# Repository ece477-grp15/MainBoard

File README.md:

# SeniorDesignMainBoard
The main PCB board to run our project

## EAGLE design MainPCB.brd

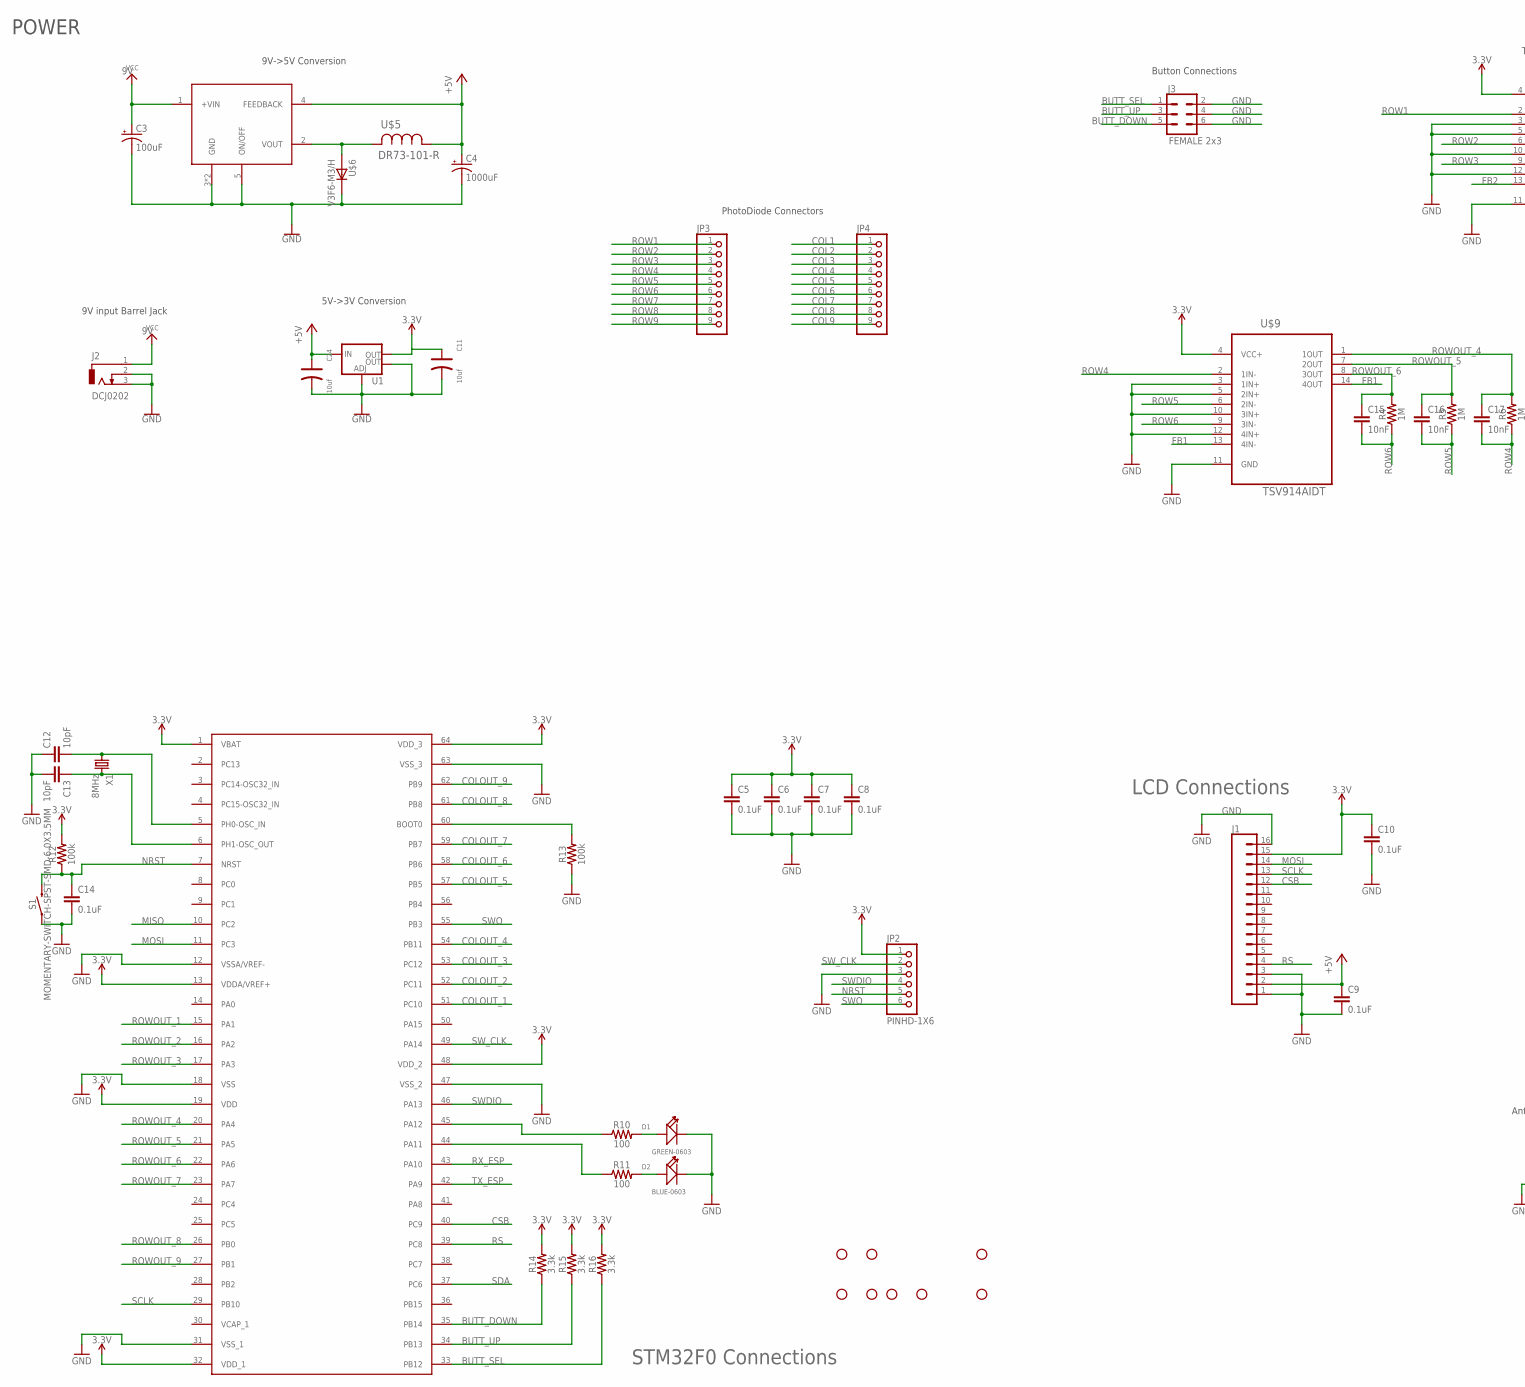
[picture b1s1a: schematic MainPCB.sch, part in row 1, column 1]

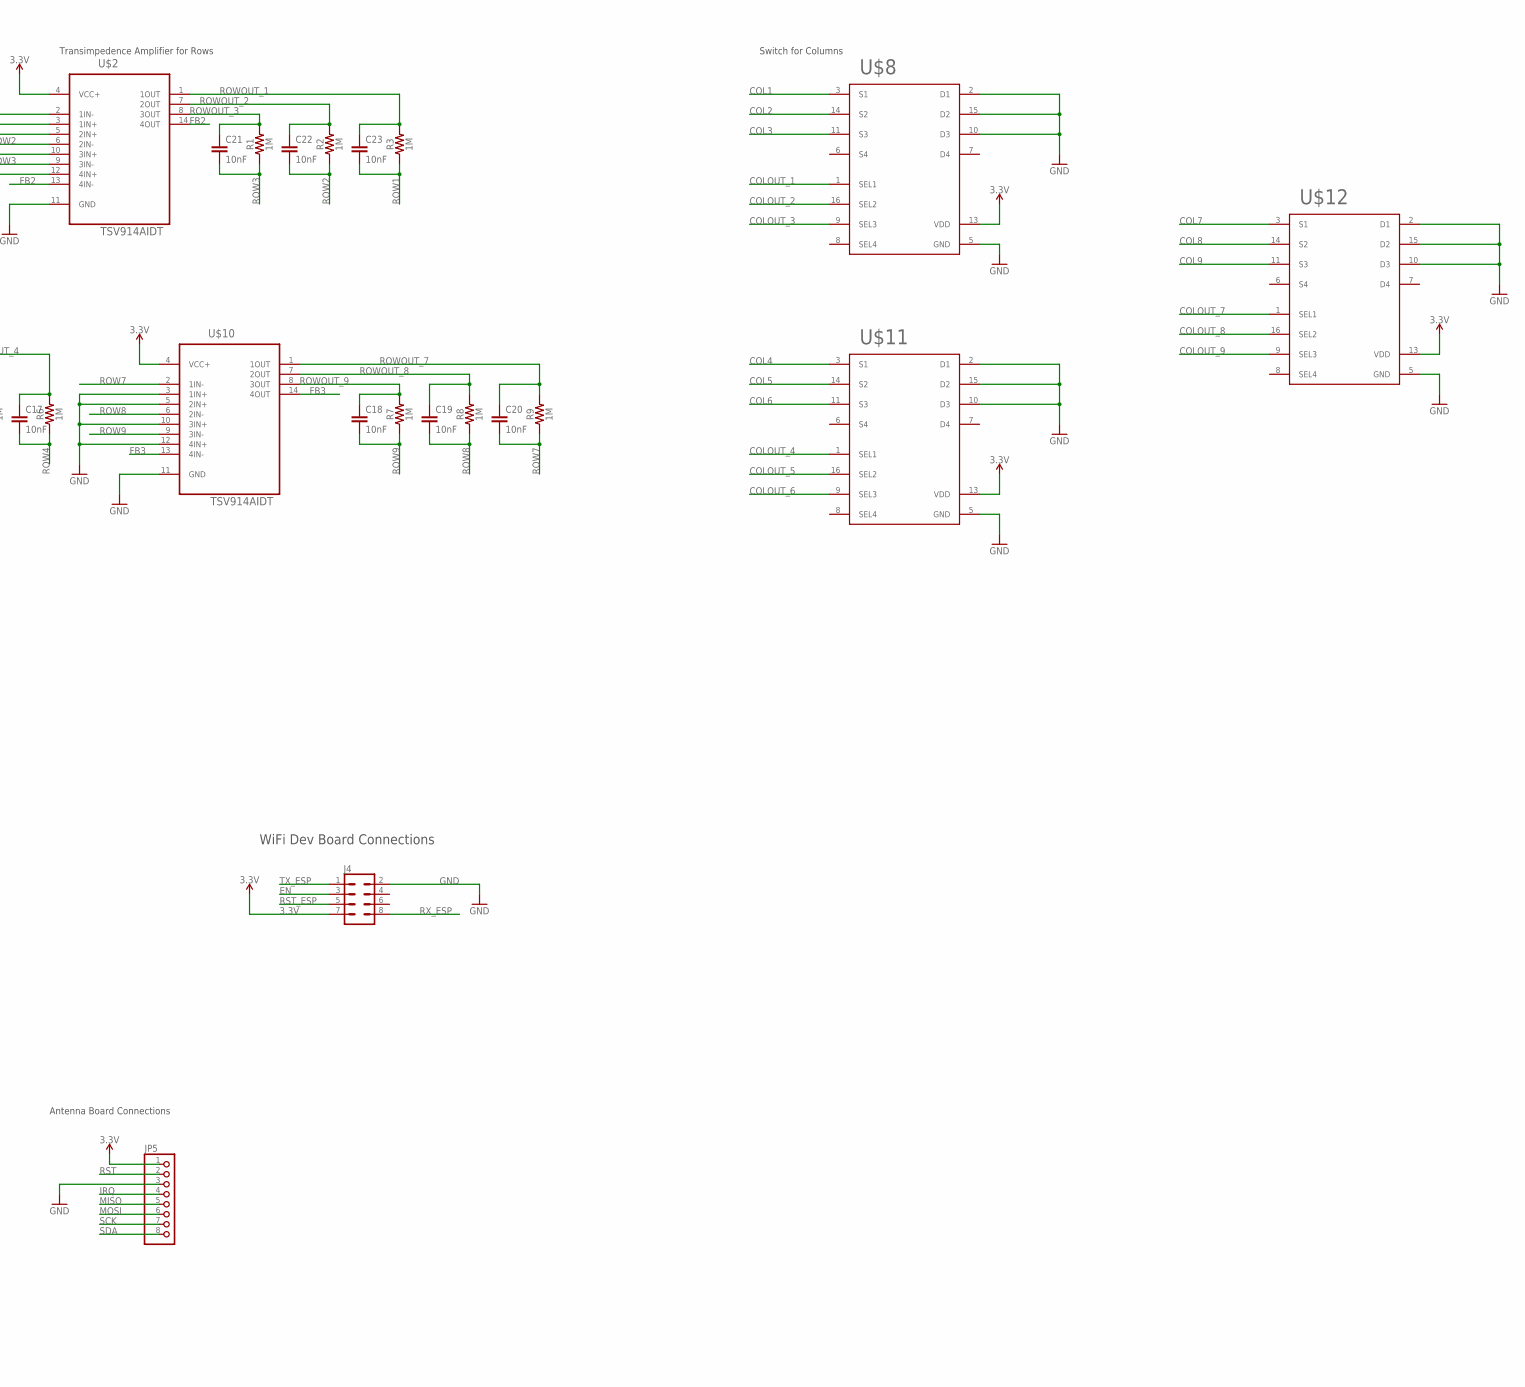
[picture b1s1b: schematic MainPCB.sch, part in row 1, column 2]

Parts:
C3: 100uF; PANASONIC_D
C4: 1000uF; PANASONIC_D
C5, C6, C7, C8, C9, C10, C14: 0.1uF; 0603
C11, C24: 10uf; AVX-A
C12, C13: 10pF; 0805
C15, C16, C17, C18, C19, C20, C21, C22, C23: 10nF; 0603
D1: GREEN-0603; LED-0603
D2: BLUE-0603; LED-0603
H2, H3, H4, H6, H7, H8, H9, H10: STAND-OFF
J1: CONN_161X16_NO_SILK; 1X16_NO_SILK
J2: DCJ0202
J3: FEMALE 2x3; 2X3
J4: CONN_04X2; 2X4
JP2: PINHD-1X6; 1X06
JP3, JP4: PINHD-1X9; 1X09
JP5: PINHD-1X8; 1X08
R1, R2, R3, R4, R5, R6, R7, R8, R9: 1M; 0603
R10, R11: 100; 0603
R12, R13: 100k; 0603
R14, R15, R16: 3.3k; 0603
S1: MOMENTARY-SWITCH-SPST-SMD-6.0X3.5MM; TACTILE_SWITCH_SMD_6.0X3.5MM
U1: V_REG_LM1117SOT223; SOT223
U$1: STM32F410R8T6; TQFP64
U$2, U$9, U$10: TSV914AIDT; SOIC-14
U$3: LM2576; DDPAK/TO-263-5
U$5: DR73-101-R; INDUCTOR_NONSTANDARD
U$6: V3F6-M3/H; DO-219AB
U$8, U$11, U$12: TMUX1112PWR; 16-TSSOP
X1: 8MHz; HC49

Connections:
3.3V: C5.1, C6.1, C7.1, C8.1, C10.1, C11.+, J1.15, J4.7, JP2.1, JP5.1, R12.2, R14.2, R15.2, R16.2, U1.2 (OUT), U$1.1 (VBAT), U$1.13 (VDDA/VREF+), U$1.19 (VDD), U$1.32 (VDD_1), U$1.48 (VDD_2), U$1.64 (VDD_3), U$2.4 (VCC+), U$8.13 (VDD), U$9.4 (VCC+), U$10.4 (VCC+), U$11.13 (VDD), U$12.13 (VDD)
9V: C3.+, J2.1, U$3.1 (+VIN)
+5V: C4.+, C9.1, C24.+, J1.2, U1.3 (IN), U$3.4 (FEEDBACK), U$5.1
BUTT_DOWN: J3.5, R14.1, U$1.35 (PB14)
BUTT_SEL: J3.1, R16.1, U$1.33 (PB12)
BUTT_UP: J3.3, R15.1, U$1.34 (PB13)
COL1: JP4.1, U$8.3 (S1)
COL2: JP4.2, U$8.14 (S2)
COL3: JP4.3, U$8.11 (S3)
COL4: JP4.4, U$11.3 (S1)
COL5: JP4.5, U$11.14 (S2)
COL6: JP4.6, U$11.11 (S3)
COL7: JP4.7, U$12.3 (S1)
COL8: JP4.8, U$12.14 (S2)
COL9: JP4.9, U$12.11 (S3)
COLOUT_1: U$1.51 (PC10), U$8.1 (SEL1)
COLOUT_2: U$1.52 (PC11), U$8.16 (SEL2)
COLOUT_3: U$1.53 (PC12), U$8.9 (SEL3)
COLOUT_4: U$1.54 (PB11), U$11.1 (SEL1)
COLOUT_5: U$1.57 (PB5), U$11.16 (SEL2)
COLOUT_6: U$1.58 (PB6), U$11.9 (SEL3)
COLOUT_7: U$1.59 (PB7), U$12.1 (SEL1)
COLOUT_8: U$1.61 (PB8), U$12.16 (SEL2)
COLOUT_9: U$1.62 (PB9), U$12.9 (SEL3)
CSB: J1.12, U$1.40 (PC9)
EN: J4.3
FB1: U$9.13 (4IN-), U$9.14 (4OUT)
FB2: U$2.13 (4IN-), U$2.14 (4OUT)
FB3: U$10.13 (4IN-), U$10.14 (4OUT)
GND: C3.-, C4.-, C5.2, C6.2, C7.2, C8.2, C9.2, C10.2, C11.-, C12.1, C13.2, C14.2, C24.-, D1.-, D2.-, J1.1, J1.3, J1.16, J2.2, J2.3, J3.2, J3.4, J3.6, J4.2, JP2.3, JP5.3, R13.1, S1.1, U1.1 (ADJ), U1.4 (OUT), U$1.12 (VSSA/VREF-), U$1.18 (VSS), U$1.31 (VSS_1), U$1.47 (VSS_2), U$1.63 (VSS_3), U$2.3 (1IN+), U$2.5 (2IN+), U$2.10 (3IN+), U$2.11 (GND), U$2.12 (4IN+), U$3.3 (GND), U$3.5 (ON/OFF), U$3.6 (GND), U$6.C, U$8.2 (D1), U$8.5 (GND), U$8.10 (D3), U$8.15 (D2), U$9.3 (1IN+), U$9.5 (2IN+), U$9.10 (3IN+), U$9.11 (GND), U$9.12 (4IN+), U$10.3 (1IN+), U$10.5 (2IN+), U$10.10 (3IN+), U$10.11 (GND), U$10.12 (4IN+), U$11.2 (D1), U$11.5 (GND), U$11.10 (D3), U$11.15 (D2), U$12.2 (D1), U$12.5 (GND), U$12.10 (D3), U$12.15 (D2)
IRQ: JP5.4
MISO: JP5.5, U$1.10 (PC2)
MOSI: J1.14, JP5.6, U$1.11 (PC3)
unnamed: C12.2, U$1.5 (PH0-OSC_IN), X1.1
unnamed: C13.1, U$1.6 (PH1-OSC_OUT), X1.2
unnamed: U$3.2 (VOUT), U$5.2, U$6.A
unnamed: R10.1, U$1.45 (PA12)
unnamed: D1.+, R10.2
unnamed: R11.1, U$1.44 (PA11)
unnamed: D2.+, R11.2
unnamed: R13.2, U$1.60 (BOOT0)
NRST: C14.1, JP2.5, R12.1, S1.2, U$1.7 (NRST)
ROW1: C23.2, JP3.1, R3.1, U$2.2 (1IN-)
ROW2: C22.2, JP3.2, R2.1, U$2.6 (2IN-)
ROW3: C21.2, JP3.3, R1.1, U$2.9 (3IN-)
ROW4: C17.2, JP3.4, R6.1, U$9.2 (1IN-)
ROW5: C16.2, JP3.5, R5.1, U$9.6 (2IN-)
ROW6: C15.2, JP3.6, R4.1, U$9.9 (3IN-)
ROW7: C20.2, JP3.7, R9.1, U$10.2 (1IN-)
ROW8: C19.2, JP3.8, R8.1, U$10.6 (2IN-)
ROW9: C18.2, JP3.9, R7.1, U$10.9 (3IN-)
ROWOUT_1: C23.1, R3.2, U$1.15 (PA1), U$2.1 (1OUT)
ROWOUT_2: C22.1, R2.2, U$1.16 (PA2), U$2.7 (2OUT)
ROWOUT_3: C21.1, R1.2, U$1.17 (PA3), U$2.8 (3OUT)
ROWOUT_4: C17.1, R6.2, U$1.20 (PA4), U$9.1 (1OUT)
ROWOUT_5: C16.1, R5.2, U$1.21 (PA5), U$9.7 (2OUT)
ROWOUT_6: C15.1, R4.2, U$1.22 (PA6), U$9.8 (3OUT)
ROWOUT_7: C20.1, R9.2, U$1.23 (PA7), U$10.1 (1OUT)
ROWOUT_8: C19.1, R8.2, U$1.26 (PB0), U$10.7 (2OUT)
ROWOUT_9: C18.1, R7.2, U$1.27 (PB1), U$10.8 (3OUT)
RS: J1.4, U$1.39 (PC8)
RST: JP5.2
RST_ESP: J4.5
RX_ESP: J4.8, U$1.43 (PA10)
SCK: JP5.7
SCLK: J1.13, U$1.29 (PB10)
SDA: JP5.8, U$1.37 (PC6)
SWDIO: JP2.4, U$1.46 (PA13)
SWO: JP2.6, U$1.55 (PB3)
SW_CLK: JP2.2, U$1.49 (PA14)
TX_ESP: J4.1, U$1.42 (PA9)

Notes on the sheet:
STM32F0 Connections
LCD Connections
POWER
9V input Barrel Jack
5V->3V Conversion
9V->5V Conversion
Transimpedence Amplifier for Rows
Switch for Columns
Antenna Board Connections
PhotoDiode Connectors
Button Connections
WiFi Dev Board Connections

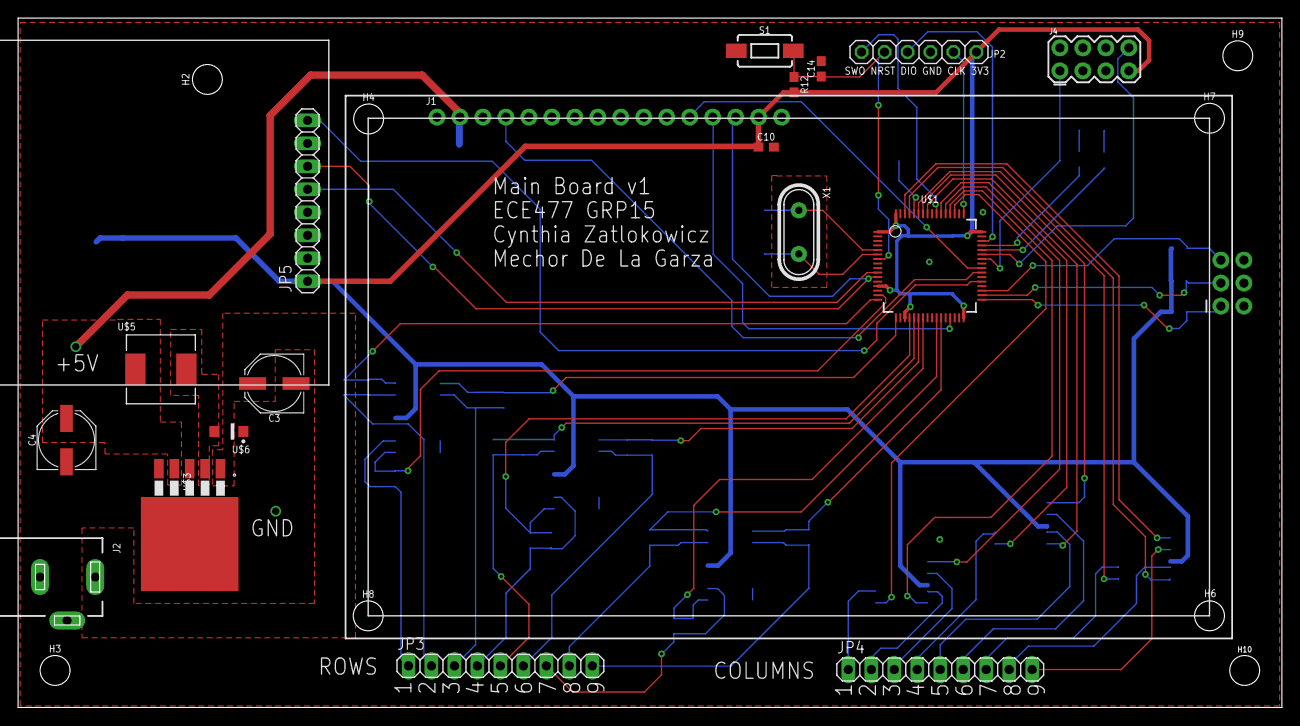
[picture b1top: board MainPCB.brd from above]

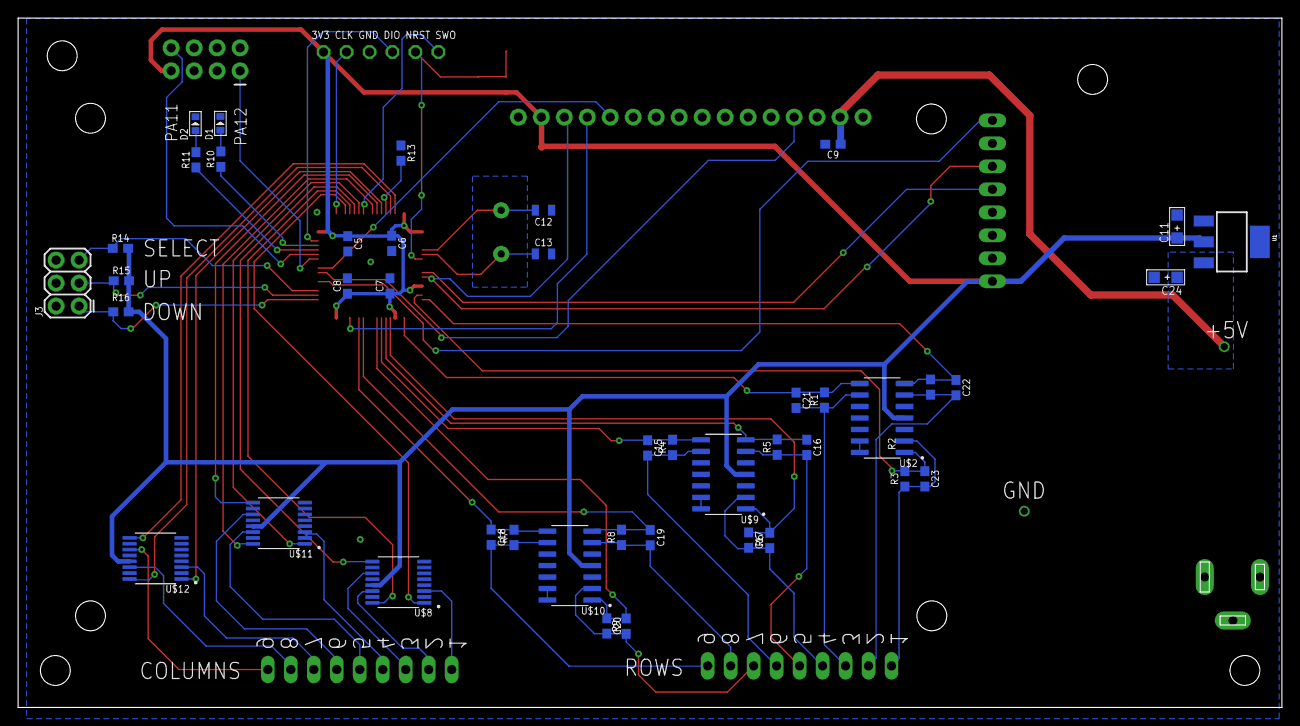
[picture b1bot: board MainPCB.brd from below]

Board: 2 copper layers, 139.7 x 76.2 mm, 69 parts (43 on the bottom side), 66 nets.

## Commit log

2020-02-11 added eagle schematic
2020-02-12 put on STM
2020-02-19 added LCD connector
2020-02-19 added lcd connections
2020-02-21 started building the circuits
2020-02-22 added connections
2020-02-26 fixin the things
2020-03-02 added bypass capcitors
2020-03-02 added various parts
2020-03-04 yayyy pinsssss
2020-03-04 added reset switch
2020-03-04 added some pins for buttons
    also changed the layout slightly
2020-03-04 the finer things
2020-03-05 schematic DONE
2020-03-05 routing blows
2020-03-05 changed layout
2020-03-06 half routed
2020-03-06 savey save saved save
2020-03-06 she done
2020-03-13 major changes
2020-03-13 lotta changes
2020-03-14 3.3V reguator
2020-03-14 yay purty

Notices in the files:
parts and their libraries:
SparkFun-Capacitors: Licensing: Creative Commons ShareAlike 4.0 International - https://creativecommons.org/licenses/by-sa/4.0
